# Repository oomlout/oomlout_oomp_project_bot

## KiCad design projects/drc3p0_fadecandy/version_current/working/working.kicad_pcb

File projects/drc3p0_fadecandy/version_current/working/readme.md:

# fadecandy by Drc3p0  
This is a harvested standardized copy of a project from github.  
The original project can be found at:  
https://github.com/Drc3p0/fadecandy  
Please consult that link for additional, details, files, and license information.  
Note: It was auto harvested and if the original repo had more than one board file or anything out of the ordinary the files here are likely not representative.

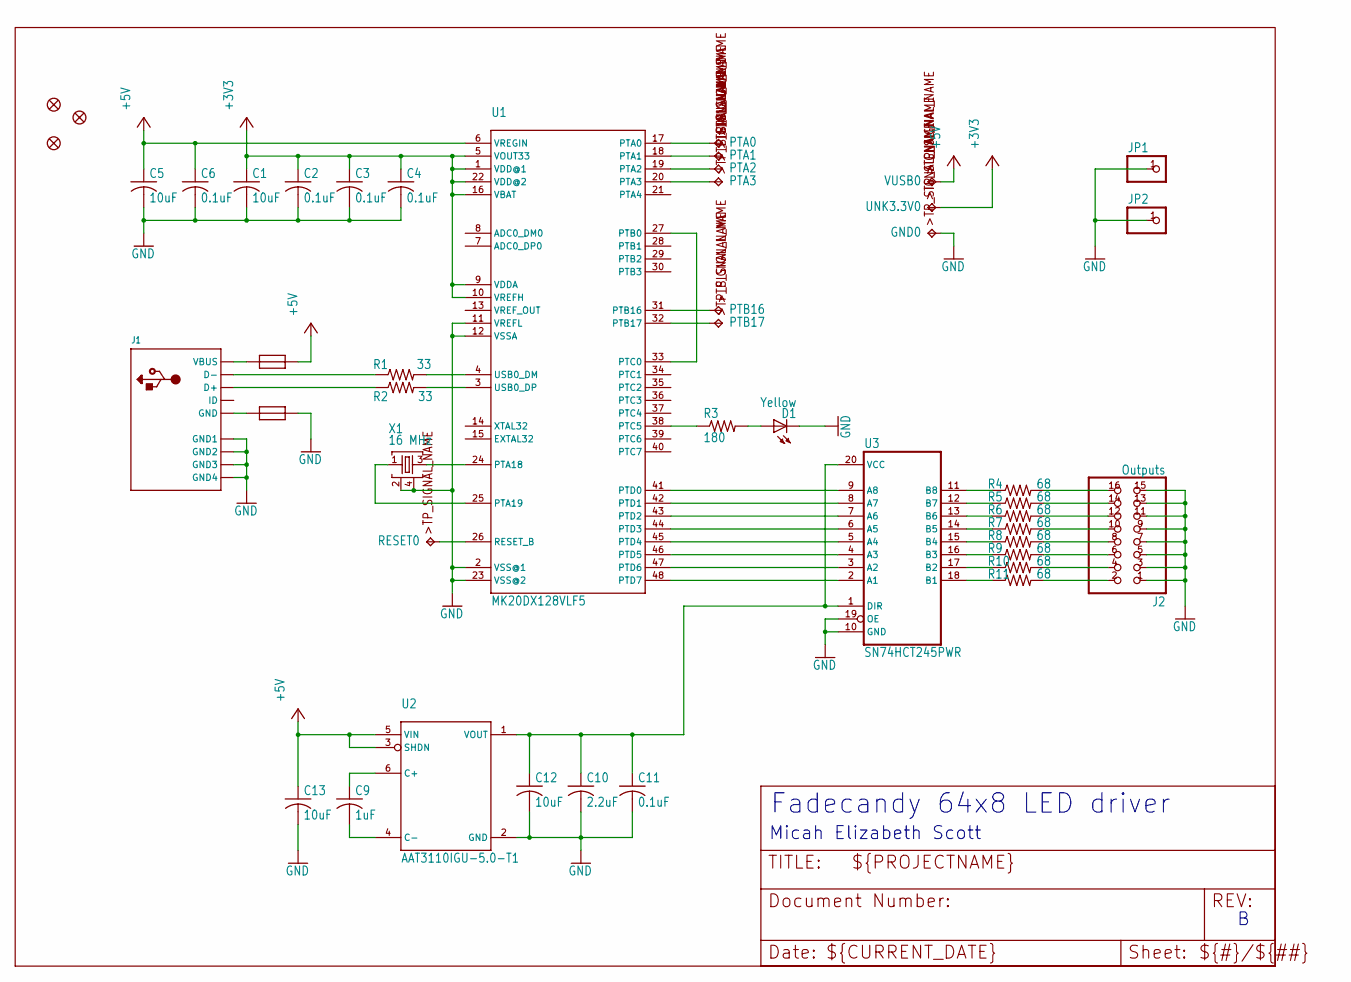
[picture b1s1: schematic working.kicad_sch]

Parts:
C1, C5, C12, C13: 10uF; 0805
C2, C3, C4, C6, C11: 0.1uF; 0805
C9: 1uF; 0805
C10: 2.2uF; 0805
D1: Yellow; CHIP-LED0805
FB1, FB2: FB0805/NO-OUTLINE; 0805
FID1, FID2, FID3: FIDUCIAL""; FIDUCIAL_1MM
GND0: TPTP18SQ; TP18SQ
J1: USBMINIB; USB-MINIB
J2: Outputs; 2X08
JP1, JP2: PINHD-1X1; 1X01
PTA0, PTA1, PTA2, PTA3: TPTP18SQ; TP18SQ
PTB16, PTB17: TPTP18SQ; TP18SQ
R1, R2: 33; 0805
R3: 180; 0805
R4, R5, R6, R7, R8, R9, R10, R11: 68; 0805
RESET0: TPTP18SQ; TP18SQ
U1: MK20DX128VLF5; LQFP48
U2: AAT3110IGU-5.0-T1; SOT23-6L
U3: SN74HCT245PWR; TSSOP20
UNK3.3V0: TPTP18SQ; TP18SQ
VUSB0: TPTP18SQ; TP18SQ
X1: 16 MHz; TSX-3225

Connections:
+3V3: C1.1, C2.1, C3.1, C4.1, U1.1 (VDD@1), U1.5 (VOUT33), U1.9 (VDDA), U1.10 (VREFH), U1.16 (VBAT), U1.22 (VDD@2), UNK3.3V0.TP
+5V: C5.1, C6.1, C13.1, FB1.2, U1.6 (VREGIN), U2.3 (SHDN), U2.5 (VIN), VUSB0.TP
GND: C1.2, C2.2, C3.2, C4.2, C5.2, C6.2, C10.2, C11.2, C12.2, C13.2, D1.C, FB2.2, GND0.TP, J1.GND1, J1.GND2, J1.GND3, J1.GND4, J2.1, J2.3, J2.5, J2.7, J2.9, J2.11, J2.13, J2.15, JP1.1, JP2.1, U1.2 (VSS@1), U1.11 (VREFL), U1.12 (VSSA), U1.23 (VSS@2), U2.2 (GND), U3.10 (GND), U3.19 (OE), X1.2, X1.4
unnamed: R3.1, U1.38 (PTC5)
unnamed: U1.24 (PTA18), X1.3
unnamed: D1.A, R3.2
unnamed: U1.25 (PTA19), X1.1
unnamed: FB1.1, J1.VBUS
unnamed: U1.27 (PTB0), U1.33 (PTC0)
unnamed: FB2.1, J1.GND
unnamed: U1.41 (PTD0), U3.9 (A8)
unnamed: J1.D-, R1.1
unnamed: J1.D+, R2.1
unnamed: R1.2, U1.4 (USB0_DM)
unnamed: R2.2, U1.3 (USB0_DP)
unnamed: U1.42 (PTD1), U3.8 (A7)
unnamed: U1.43 (PTD2), U3.7 (A6)
unnamed: U1.44 (PTD3), U3.6 (A5)
unnamed: U1.45 (PTD4), U3.5 (A4)
unnamed: U1.46 (PTD5), U3.4 (A3)
unnamed: U1.47 (PTD6), U3.3 (A2)
unnamed: U1.48 (PTD7), U3.2 (A1)
unnamed: R4.1, U3.11 (B8)
unnamed: C9.1, U2.6 (C+)
unnamed: C9.2, U2.4 (C-)
unnamed: R5.1, U3.12 (B7)
unnamed: R6.1, U3.13 (B6)
unnamed: R7.1, U3.14 (B5)
unnamed: R8.1, U3.15 (B4)
unnamed: C10.1, C11.1, C12.1, U2.1 (VOUT), U3.1 (DIR), U3.20 (VCC)
unnamed: R9.1, U3.16 (B3)
unnamed: R10.1, U3.17 (B2)
unnamed: R11.1, U3.18 (B1)
unnamed: J2.16, R4.2
unnamed: J2.14, R5.2
unnamed: J2.12, R6.2
unnamed: J2.10, R7.2
unnamed: J2.8, R8.2
unnamed: J2.6, R9.2
unnamed: J2.4, R10.2
unnamed: J2.2, R11.2
unnamed: RESET0.TP, U1.26 (RESET_B)
unnamed: PTA0.TP, U1.17 (PTA0)
unnamed: PTA1.TP, U1.18 (PTA1)
unnamed: PTA2.TP, U1.19 (PTA2)
unnamed: PTA3.TP, U1.20 (PTA3)
unnamed: PTB16.TP, U1.31 (PTB16)
unnamed: PTB17.TP, U1.32 (PTB17)

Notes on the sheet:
Micah Elizabeth Scott
Fadecandy 64x8 LED driver

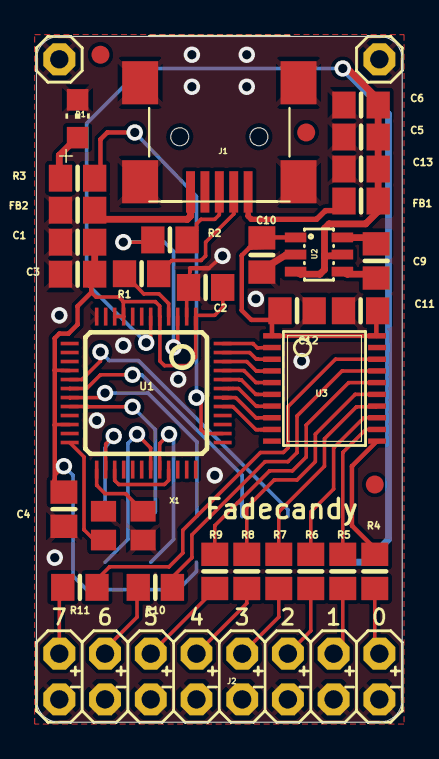
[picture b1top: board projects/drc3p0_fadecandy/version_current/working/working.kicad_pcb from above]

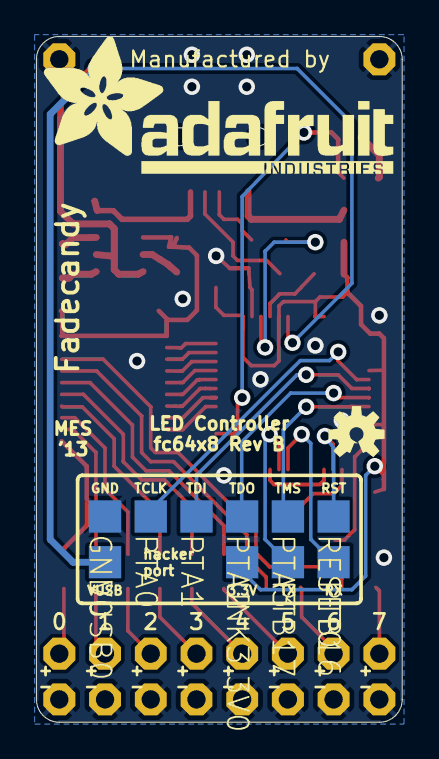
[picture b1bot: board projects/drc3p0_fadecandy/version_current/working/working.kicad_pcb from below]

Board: 16 copper layers, 20.3 x 38.1 mm, 48 parts (12 on the bottom side), 48 nets.

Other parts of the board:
U$1: OSHW-LOGO-S
U$2: ADAFRUIT_TEXT_20MM

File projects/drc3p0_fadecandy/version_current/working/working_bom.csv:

"Id";"Designator";"Footprint";"Quantity";"Designation";"Supplier and ref";
1;"R2,R1";"0805";2;"33";;;
2;"C4,C3,C11,C6,C2";"0805";5;"0.1uF";;;
3;"U3";"TSSOP20";1;"SN74HCT245PWR";;;
4;"FID2,FID1,FID3";"FIDUCIAL_1MM";3;"FIDUCIAL""";;;
5;"JP1,JP2";"1X01";2;"";;;
6;"U1";"LQFP48";1;"MK20DX128VLF5";;;
7;"R10,R6,R5,R8,R7,R11,R9,R4";"0805";8;"68";;;
8;"J2";"2X08";1;"Outputs";;;
9;"C13,C1,C5,C12";"0805";4;"10uF";;;
10;"J1";"USB-MINIB";1;"";;;
11;"R3";"0805";1;"180";;;
12;"X1";"TSX-3225";1;"16 MHz";;;
13;"FB2,FB1";"0805";2;"FB0805/NO-OUTLINE";;;
14;"D1";"CHIP-LED0805";1;"Yellow";;;
15;"C9";"0805";1;"1uF";;;
16;"C10";"0805";1;"2.2uF";;;
17;"U2";"SOT23-6L";1;"AAT3110IGU-5.0-T1";;;
18;"PTB17,VUSB0,RESET0,UNK3.3V0,PTA2,PTA1,PTB16,PTA0,GND0,PTA3";"TP18SQ";10;"TPTP18SQ";;;
19;"U$1";"OSHW-LOGO-S";1;"";;;
20;"U$2";"ADAFRUIT_TEXT_20MM";1;"";;;

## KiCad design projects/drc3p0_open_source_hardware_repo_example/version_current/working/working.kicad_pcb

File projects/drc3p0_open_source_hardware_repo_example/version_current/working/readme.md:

# open-source-hardware-repo-example by Drc3p0  
This is a harvested standardized copy of a project from github.  
The original project can be found at:  
https://github.com/Drc3p0/open-source-hardware-repo-example  
Please consult that link for additional, details, files, and license information.  
Note: It was auto harvested and if the original repo had more than one board file or anything out of the ordinary the files here are likely not representative.

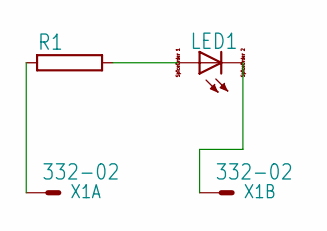
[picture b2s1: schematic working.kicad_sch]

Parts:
LED1: LED_ELD260; LED_LD260
R1: RAC01; AC01
X1: 332-02

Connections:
unnamed: LED1.A, R1.2
unnamed: R1.1, X1.1
unnamed: LED1.K (C), X1.2

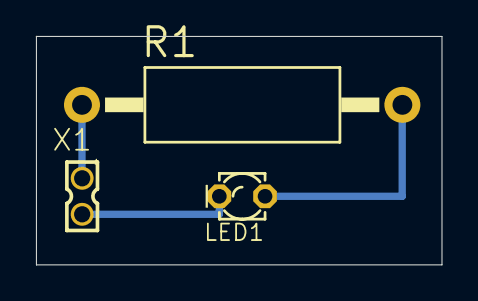
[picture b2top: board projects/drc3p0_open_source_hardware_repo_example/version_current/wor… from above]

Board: 2 copper layers, 22.5 x 12.7 mm, 3 parts (0 on the bottom side), 3 nets.

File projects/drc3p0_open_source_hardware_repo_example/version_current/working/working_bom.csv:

"Id";"Designator";"Footprint";"Quantity";"Designation";"Supplier and ref";
1;"X1";"332-02";1;"332-02";;;
2;"R1";"AC01";1;"";;;
3;"LED1";"LED_LD260";1;"";;;

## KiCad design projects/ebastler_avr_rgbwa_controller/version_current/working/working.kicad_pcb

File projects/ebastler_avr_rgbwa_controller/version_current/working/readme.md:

# AVR-RGBWA-Controller by ebastler  
This is a harvested standardized copy of a project from github.  
The original project can be found at:  
https://github.com/ebastler/AVR-RGBWA-Controller  
Please consult that link for additional, details, files, and license information.  
Note: It was auto harvested and if the original repo had more than one board file or anything out of the ordinary the files here are likely not representative.

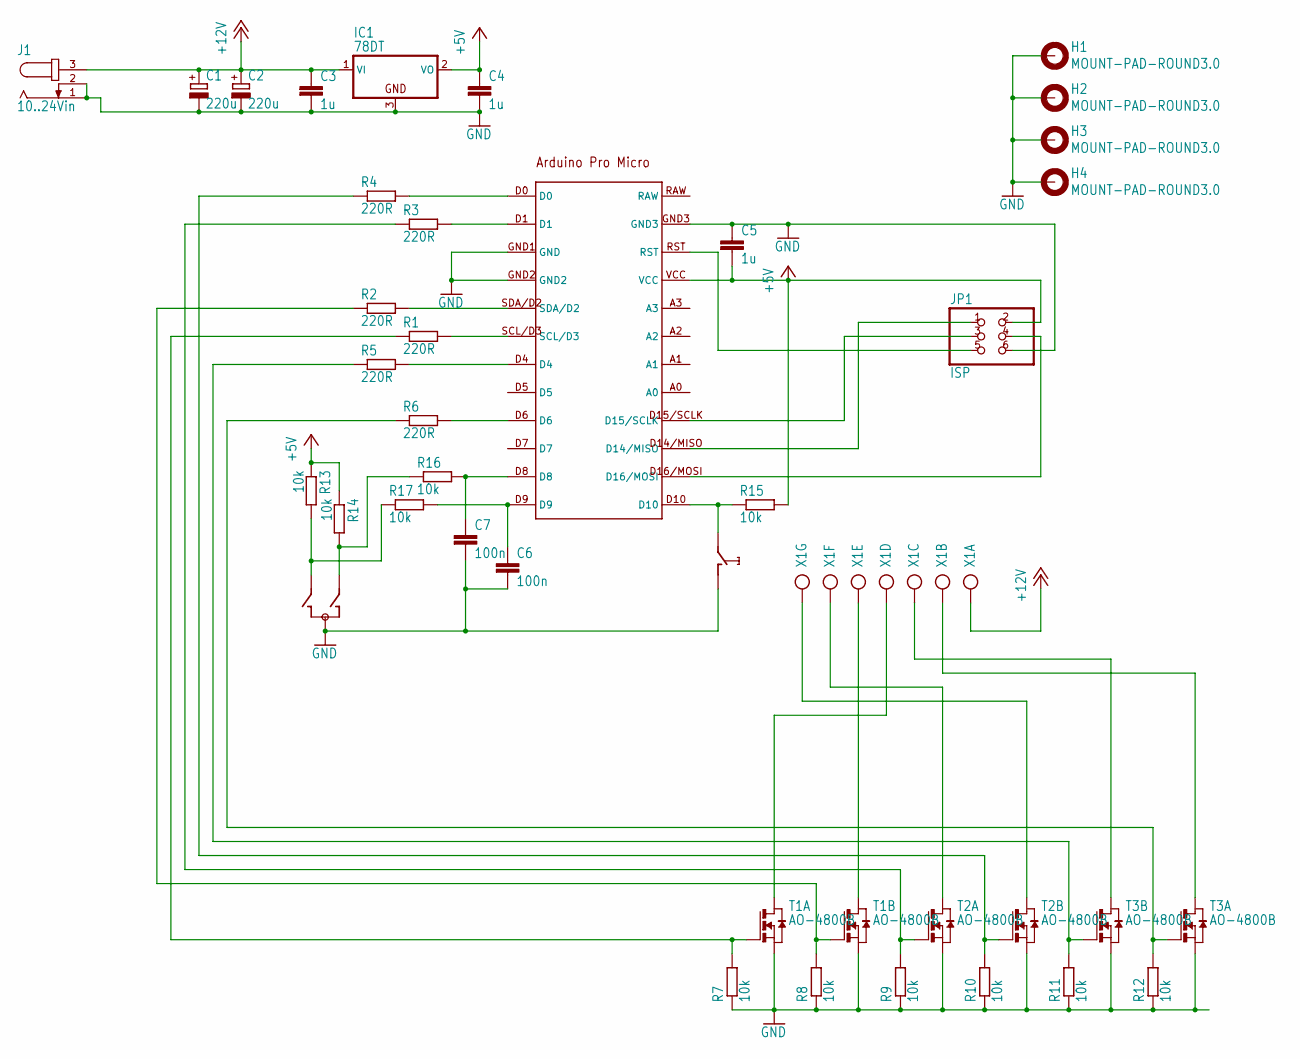
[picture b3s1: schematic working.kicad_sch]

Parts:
C1, C2: 220u; 150CLZ-1010
C3, C4, C5: 1u; C1206
C6, C7: 100n; C0805
H1, H2, H3, H4: MOUNT-PAD-ROUND3.0; 3,0-PAD
IC1: 78DT; TO252
J1: 10..24Vin; SPC4078
JP1: ISP; 2X03
R1, R2, R3, R4, R5, R6: 220R; M0805
R7, R8, R9, R10, R11, R12, R13, R14, R15, R16, R17: 10k; M0805
SW1: EC12E_SW; ALPS_EC12E_SW
T1, T2, T3: AO-4800B; SM8
U$1: PROMICRO
X1: AK300/7; AK300_7

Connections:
+5V: C4.1, C5.2, IC1.2 (VO), JP1.2, R13.1, R14.1, R15.2, U$1.VCC
+12V: C1.+, C2.+, C3.1, IC1.1 (VI), J1.3, X1.1
GND: C1.-, C2.-, C3.2, C4.2, C5.1, C6.2, C7.2, H1.B3,0, H2.B3,0, H3.B3,0, H4.B3,0, IC1.3 (GND), J1.1, J1.2, JP1.6, R7.1, R8.1, R9.1, R10.1, R11.1, R12.1, SW1.C, SW1.D (1), T1.1 (S), T1.3 (S), T2.1 (S), T2.3 (S), T3.1 (S), T3.3 (S), U$1.GND1 (GND), U$1.GND2, U$1.GND3
unnamed: R4.2, U$1.D0
unnamed: R3.2, U$1.D1
unnamed: R2.2, U$1.SDA/D2
unnamed: R1.2, U$1.SCL/D3
unnamed: R5.2, U$1.D4
unnamed: R6.2, U$1.D6
unnamed: R1.1, R7.2, T1.2 (G)
unnamed: R2.1, R8.2, T1.4 (G)
unnamed: R3.1, R9.2, T2.2 (G)
unnamed: R4.1, R10.2, T2.4 (G)
unnamed: R5.1, R11.2, T3.4 (G)
unnamed: R6.1, R12.2, T3.2 (G)
unnamed: R13.2, R17.1, SW1.B
unnamed: JP1.1, U$1.D14/MISO
unnamed: T3.7 (D), T3.8 (D), X1.2
unnamed: T1.5 (D), T1.6 (D), X1.5
unnamed: T1.7 (D), T1.8 (D), X1.4
unnamed: R14.2, R16.1, SW1.A
unnamed: JP1.3, U$1.D15/SCLK
unnamed: C6.1, R17.2, U$1.D9
unnamed: R15.1, SW1.E (2), U$1.D10
unnamed: C7.1, R16.2, U$1.D8
unnamed: JP1.5, U$1.RST
unnamed: T3.5 (D), T3.6 (D), X1.3
unnamed: T2.5 (D), T2.6 (D), X1.7
unnamed: T2.7 (D), T2.8 (D), X1.6
unnamed: JP1.4, U$1.D16/MOSI

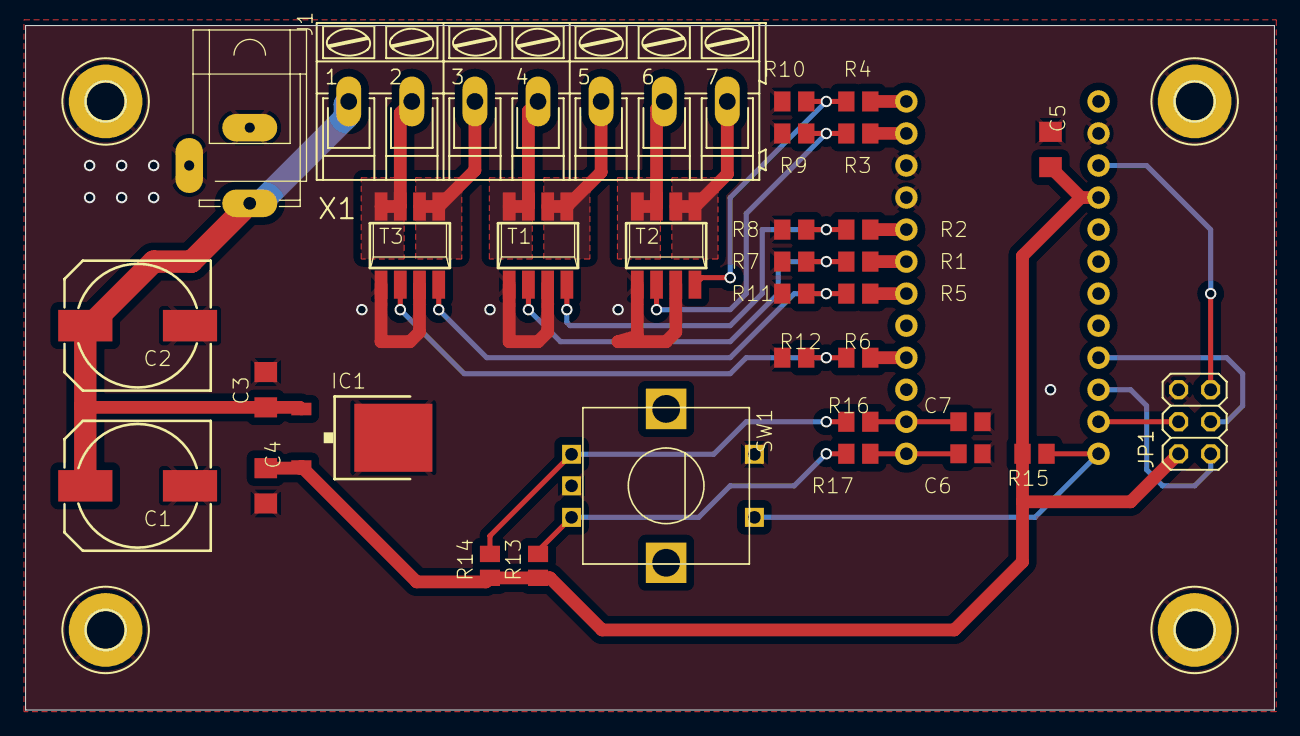
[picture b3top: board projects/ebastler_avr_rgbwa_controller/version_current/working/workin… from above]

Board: 2 copper layers, 99.0 x 54.3 mm, 37 parts (0 on the bottom side), 30 nets.

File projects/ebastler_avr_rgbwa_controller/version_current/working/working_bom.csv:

"Id";"Designator";"Footprint";"Quantity";"Designation";"Supplier and ref";
1;"T1,T2,T3";"SM8";3;"AO-4800B";;;
2;"R16,R15,R10,R7,R9,R8,R11,R17,R13,R12,R14";"M0805";11;"10k";;;
3;"R5,R3,R6,R1,R4,R2";"M0805";6;"220R";;;
4;"C1,C2";"150CLZ-1010";2;"220u";;;
5;"C5,C3,C4";"C1206";3;"1u";;;
6;"C6,C7";"C0805";2;"100n";;;
7;"H2,H4,H1,H3";"3,0-PAD";4;"MOUNT-PAD-ROUND3.0";;;
8;"X1";"AK300_7";1;"";;;
9;"JP1";"2X03";1;"ISP";;;
10;"J1";"SPC4078";1;"10..24Vin";;;
11;"SW1";"ALPS_EC12E_SW";1;"EC12E_SW";;;
12;"U$1";"PROMICRO";1;"PROMICRO";;;
13;"IC1";"TO252";1;"7805DT";;;

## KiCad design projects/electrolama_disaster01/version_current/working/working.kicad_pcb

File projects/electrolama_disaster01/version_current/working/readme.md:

# OOMP Project  
## disaster01  by electrolama  
  
oomp key: oomp_projects_flat_electrolama_disaster01  
(snippet of original readme)  
  
- disaster01  
overly blinky thing debuted at Hackaday Supercon 2019  
  
Details at [electrolama.com/p/disaster01](https://electrolama.com/p/disaster01/).  
  
  full source readme at [readme_src.md](readme_src.md)  
  
source repo at: [https://github.com/electrolama/disaster01](https://github.com/electrolama/disaster01)  
## Board  

## Schematic  

[schematic pdf](working_schematic.pdf)  
## Images

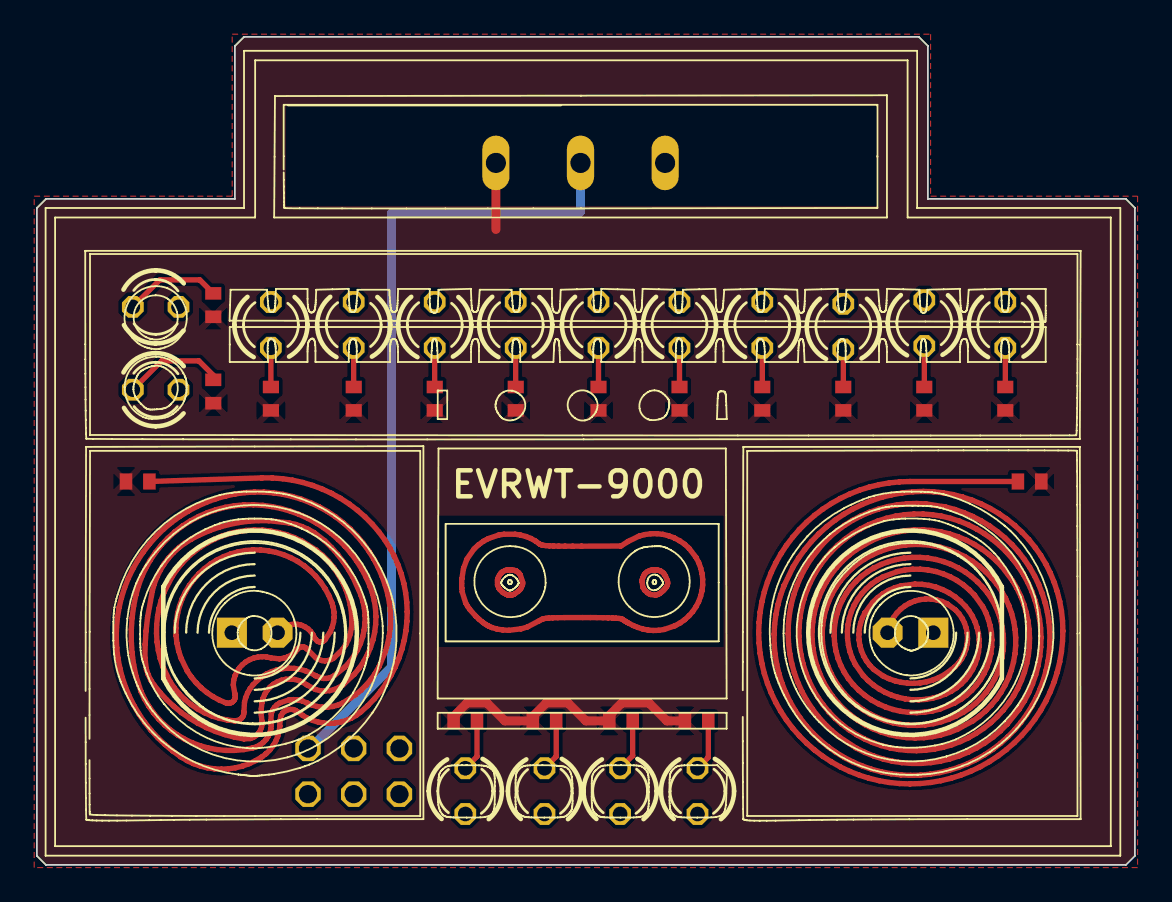
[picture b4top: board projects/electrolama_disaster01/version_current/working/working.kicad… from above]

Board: 2 copper layers, 61.0 x 46.0 mm, 38 parts (0 on the bottom side), 21 nets.

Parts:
JP1: 2X03
LED1, LED3, LED4, LED5, LED6, LED7, LED8, LED9, LED10, LED11, LED12, LED13, LED14, LED15, LED16, LED17: LED3MM
LED2, LED18: LED10MM
R1, R2, R3, R4, R5, R6, R7, R8, R9, R10, R11, R12, R13, R14, R15, R16, R17, R18: R0402
S1: 255SB

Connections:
3.3V: R1.1, R2.1, R3.1, R4.1, R5.1, R6.1, R7.1, R8.1, R9.1, R10.1, R11.1, R12.1, R13.1, R14.1, R15.1, R16.1, R17.1, R18.1, S1.1
GND: JP1.1, LED1.K, LED2.K, LED3.K, LED4.K, LED5.K, LED6.K, LED7.K, LED8.K, LED9.K, LED10.K, LED11.K, LED12.K, LED13.K, LED14.K, LED15.K, LED16.K, LED17.K, LED18.K
unnamed: LED1.A, R1.2
unnamed: LED2.A, R2.2
unnamed: LED3.A, R3.2
unnamed: LED4.A, R4.2
unnamed: LED5.A, R5.2
unnamed: LED6.A, R6.2
unnamed: LED7.A, R7.2
unnamed: LED8.A, R8.2
unnamed: LED9.A, R9.2
unnamed: LED10.A, R10.2
unnamed: LED11.A, R11.2
unnamed: LED12.A, R12.2
unnamed: LED13.A, R13.2
unnamed: LED14.A, R14.2
unnamed: LED15.A, R15.2
unnamed: LED16.A, R16.2
unnamed: LED17.A, R17.2
unnamed: LED18.A, R18.2
unnamed: JP1.2, S1.2

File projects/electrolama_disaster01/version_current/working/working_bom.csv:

"Id";"Designator";"Footprint";"Quantity";"Designation";"Supplier and ref";
1;"S1";"255SB";1;"";;;
2;"LED17,LED10,LED3,LED9,LED8,LED12,LED14,LED6,LED15,LED5,LED1,LED7,LED4,LED11,LED13,LED16";"LED3MM";16;"";;;
3;"R13,R10,R12,R9,R18,R3,R16,R4,R17,R5,R11,R1,R15,R7,R14,R8,R2,R6";"R0402";18;"";;;
4;"JP1";"2X03";1;"";;;
5;"LED2,LED18";"LED10MM";2;"";;;

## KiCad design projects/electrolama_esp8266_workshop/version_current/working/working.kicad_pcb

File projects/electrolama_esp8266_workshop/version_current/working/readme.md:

# OOMP Project  
## esp8266-workshop  by electrolama  
  
oomp key: oomp_projects_flat_electrolama_esp8266_workshop  
(snippet of original readme)  
  
- esp8266-workshop  
  
  full source readme at [readme_src.md](readme_src.md)  
  
source repo at: [https://github.com/electrolama/esp8266-workshop](https://github.com/electrolama/esp8266-workshop)  
## Board  

## Schematic  

[schematic pdf](working_schematic.pdf)  
## Images

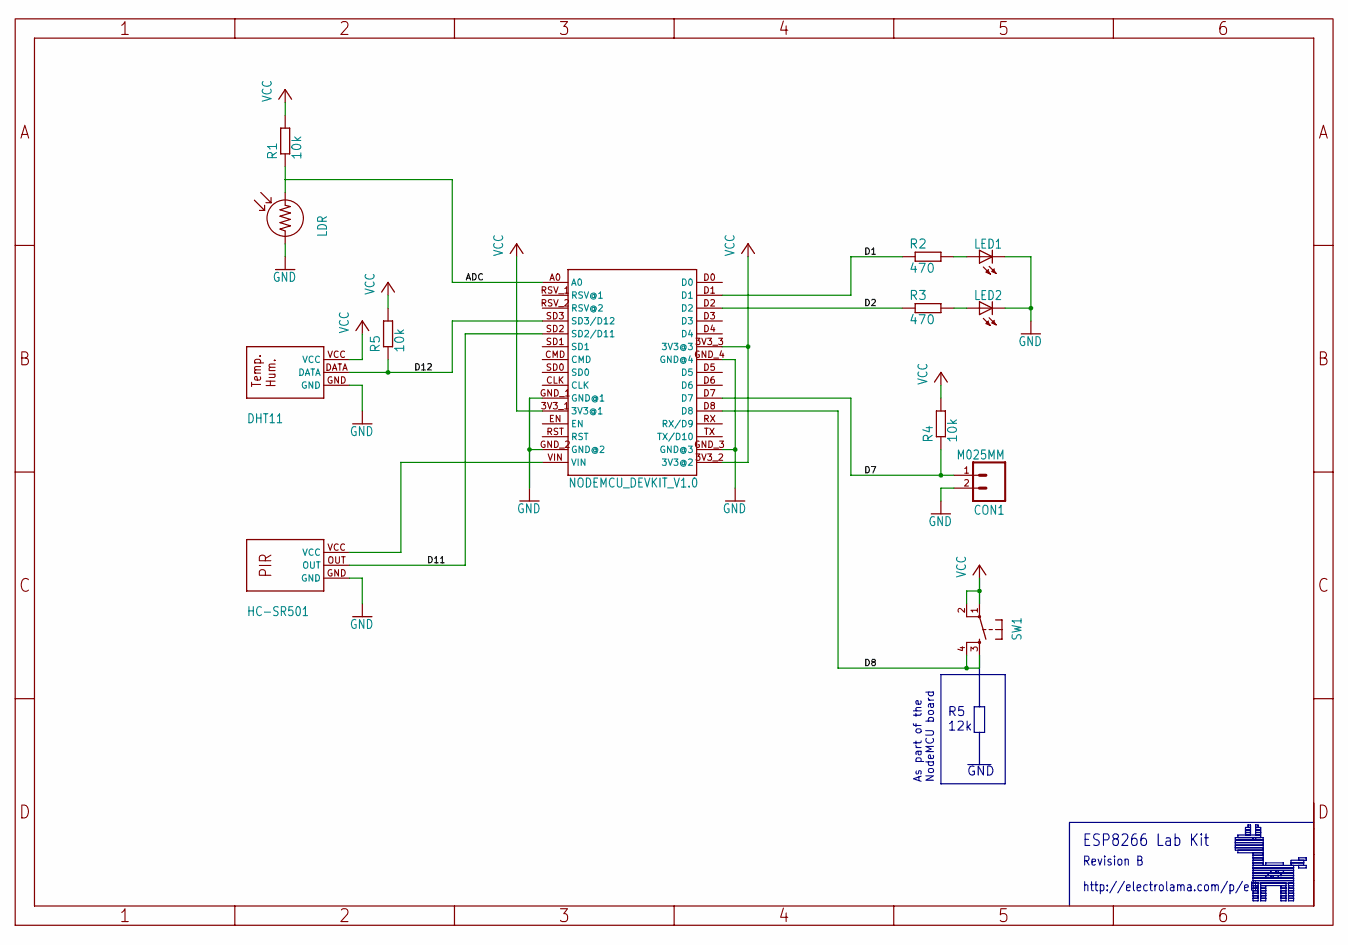
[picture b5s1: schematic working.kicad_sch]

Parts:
CON1: M025MM; SCREWTERMINAL-5MM-2
LED1, LED2: LED5MM
R1, R4, R5: 10k; RTH025W
R2, R3: 470; RTH025W
SW1: TAC_SWITCHPTH; TACTILE-PTH
U1: NODEMCU_DEVKIT_V1.0
U2: DHT11
U3: HC-SR501
VR1: LDR

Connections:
ADC: R1.1, U1.A0, VR1.2
D1: R2.1, U1.D1
D2: R3.1, U1.D2
D7: CON1.1, R4.1, U1.D7
D8: SW1.3, SW1.4, U1.D8
D11: U1.SD2 (SD2/D11), U3.OUT
D12: R5.1, U1.SD3 (SD3/D12), U2.DATA
GND: CON1.2, LED1.K (C), LED2.K (C), U1.GND_1 (GND@1), U1.GND_2 (GND@2), U1.GND_3 (GND@3), U1.GND_4 (GND@4), U2.GND, U3.GND, VR1.1
unnamed: LED1.A, R2.2
unnamed: LED2.A, R3.2
unnamed: U1.VIN, U3.VCC
VCC: R1.2, R4.2, R5.2, SW1.1, SW1.2, U1.3V3_1 (3V3@1), U1.3V3_2 (3V3@2), U1.3V3_3 (3V3@3), U2.VCC

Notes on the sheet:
Revision B
http://electrolama.com/p/elk
GND
As part of the NodeMCU board
R5 12k
ESP8266 Lab Kit

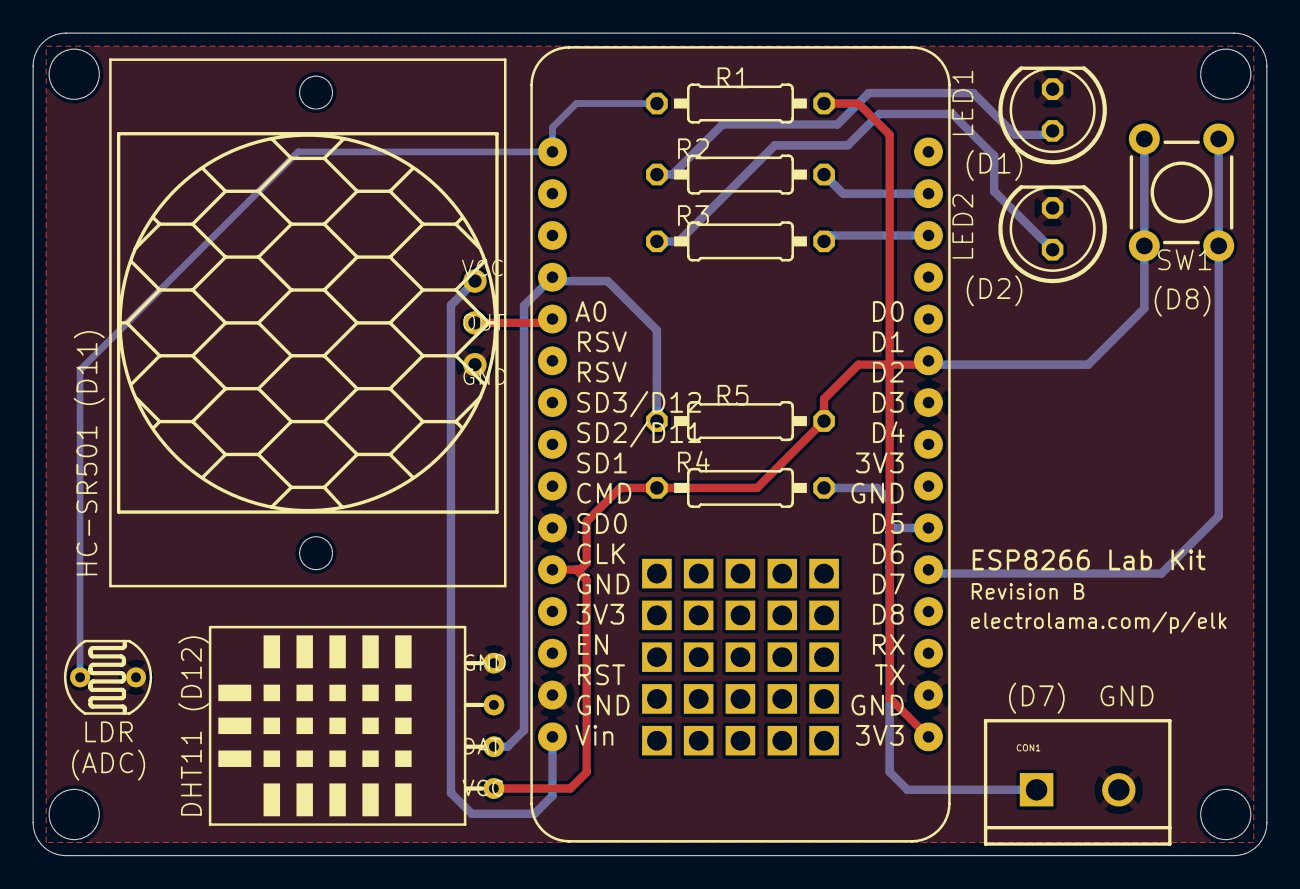
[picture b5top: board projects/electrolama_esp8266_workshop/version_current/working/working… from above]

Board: 2 copper layers, 75.0 x 50.0 mm, 18 parts (0 on the bottom side), 12 nets.

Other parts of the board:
@HOLE0, @HOLE1, @HOLE2, @HOLE3: (no value)
U$1: PROTO_VIAS_05X05-1.2; PROTO_VIAS_05X05_1.2

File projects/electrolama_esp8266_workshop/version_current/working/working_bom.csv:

Row,Description,Part,References,Value,Footprint,Quantity Per PCB,Status,Datasheet
1,,M025MM,CON1,M025MM,SCREWTERMINAL-5MM-2,1, ,
2,,LED5MM,LED1 LED2,LED5MM,LED5MM,2, ,
3,,RESISTOR-PTH-0.4,R2 R3,470,RTH025W,2, ,
4,,RESISTOR-PTH-0.4,R1 R4 R5,10k,RTH025W,3, ,
5,,TAC_SWITCHPTH,SW1,TAC_SWITCHPTH,TACTILE-PTH,1, ,
6,,DHT11,U2,DHT11,DHT11,1, ,
7,,HC-SR501,U3,HC-SR501,HC-SR501,1, ,
8,,NODEMCU_DEVKIT_V1.0,U1,NODEMCU_DEVKIT_V1.0,NODEMCU_DEVKIT_V1.0,1, ,
9,,LDR,VR1,LDR,LDR,1, ,





Project info:
Schematic:,working
Variant:,default
Revision:,
Date:,2023-08-03_17-21-23
KiCad Version:,7.0.6-7.0.6~ubuntu22.04.1
Statistics:
Component Groups:,9
Component Count:,13 (0 SMD/ 0 THT)
Fitted Components:,13 (0 SMD/ 0 THT)
Number of PCBs:,1
Total Components:,13

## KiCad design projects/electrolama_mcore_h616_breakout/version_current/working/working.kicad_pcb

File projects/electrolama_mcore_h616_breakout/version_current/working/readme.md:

# mcore-h616-breakout by electrolama  
This is a harvested standardized copy of a project from github.  
The original project can be found at:  
https://github.com/electrolama/mcore-h616-breakout  
Please consult that link for additional, details, files, and license information.  
Note: It was auto harvested and if the original repo had more than one board file or anything out of the ordinary the files here are likely not representative.

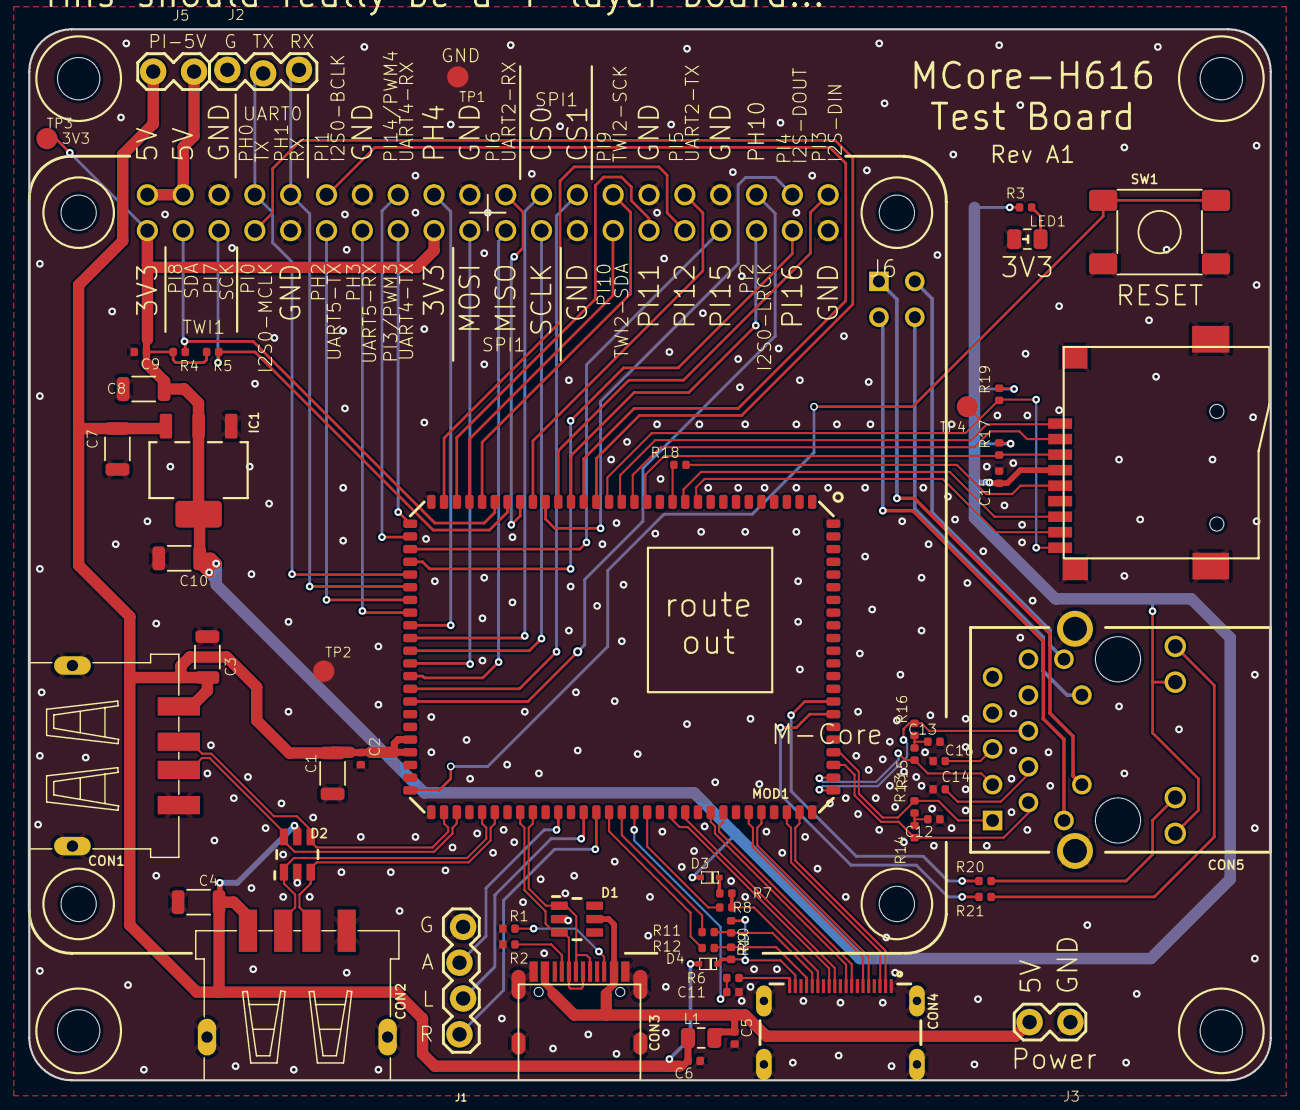
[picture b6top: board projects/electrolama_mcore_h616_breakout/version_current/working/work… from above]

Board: 2 copper layers, 88.0 x 74.5 mm, 70 parts (0 on the bottom side), 88 nets.

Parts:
@HOLE0, @HOLE1, @HOLE2, @HOLE3, @HOLE4, @HOLE5, @HOLE6, @HOLE7: (no value)
C1, C3, C4, C7, C8, C10: 47u; _PKG_C_1206
C2, C6, C9, C11, C12, C13, C14, C15, C16: 100n; _PKG_C_0402
C5: 10n; _PKG_C_0402
CON1, CON2: JING_912-121A2023S10100
CON3: USBC_C-31-M-12
CON4: C136421 - HDMI-519; 685119136923
CON5: LPJG0926HENL
CON6: C111196 - TF-15x15; TF_SHENZHEN-SPECIAL
D1, D2: SRV05-4-P-T7; SOT95P280X145-6N
D3, D4: RB520S30T1G; _PKG_SOD523
IC1: LD1117-3.3; _PKG_SOT223-4_TI-DCY4
J1: 1X04_LOCK
J2: 1X03_LOCK
J3, J5: 1X02_LOCK
J4: CON_2.54MM_TH_2X20
J6: CON_2.54MM_TH_2X2
L1: FB; _PKG_C_0805
LED1: _PKG_LED_0805
MOD1: MCORE-H616_V1
R1, R2: 5k1; _PKG_R_0402
R3, R8, R11, R12, R18, R20, R21: 100; _PKG_R_0402
R4, R5, R17, R19: 10k; _PKG_R_0402
R6: 1k; _PKG_R_0402
R7: 27k 1%; _PKG_R_0402
R9, R10: 1k8; _PKG_R_0402
R13, R14, R15, R16: 49.9Ω; _PKG_R_0402
SW1: SPNO; GENERIC_SPNO_4P_6X6MM
TP1, TP2, TP3, TP4: TP; TP_DOT_1.5X1.5MM

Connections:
5V: C1.2, C2.2, C3.2, C4.2, C6.2, C7.2, CON1.VBUS, CON2.VBUS, D2.5, D4.2, IC1.3, J5.2, L1.2, MOD1.49, MOD1.50
GND: C1.1, C2.1, C3.1, C4.1, C5.1, C6.1, C7.1, C8.1, C9.1, C10.1, C11.1, C12.1, C13.1, C14.1, C15.1, C16.1, CON1.GND, CON1.P$5, CON1.P$6, CON2.GND, CON2.P$5, CON2.P$6, CON3.GND@1, CON3.GND@2, CON3.P$1, CON3.P$2, CON3.P$3, CON3.P$4, CON3.P$5, CON3.P$6, CON3.P$7, CON3.P$8, CON4.1, CON4.4, CON4.7, CON4.10, CON4.13, CON4.SHELL, CON4.SHELL1, CON4.SHELL2, CON4.SHELL3, CON5.MH3, CON5.MH4, CON6.6, CON6.S1, CON6.S2, CON6.S3, CON6.S4, D1.2, D2.2, IC1.1, J1.1, J2.1, J3.1, J4.P$6, J4.P$9, J4.P$14, J4.P$20, J4.P$25, J4.P$30, J4.P$34, J4.P$39, LED1.C, MOD1.13, MOD1.31, MOD1.51, MOD1.52, MOD1.54, MOD1.57, MOD1.60, MOD1.63, MOD1.72, MOD1.75, MOD1.78, MOD1.81, MOD1.84, MOD1.89, MOD1.106, R1.1, R2.1, SW1.P$3, SW1.P$4, TP1.TP, TP2.TP
H5V: CON4.18, D4.1, R9.1, R10.1
HCEC: MOD1.71, R8.2
HDCEC: CON4.14, R7.1, R8.1
HDHPD: CON4.19, R6.1
HDSCL: CON4.15, R9.2, R11.1
HDSDA: CON4.16, R10.2, R12.1
HHPD: C11.2, MOD1.70, R6.2
HSCL: MOD1.69, R11.2
HSDA: MOD1.68, R12.2
HTX0_N: CON4.9, MOD1.76
HTX0_P: CON4.8, MOD1.77
HTX1_N: CON4.6, MOD1.79
HTX1_P: CON4.5, MOD1.80
HTX2_N: CON4.3, MOD1.82
HTX2_P: CON4.2, MOD1.83
HTXC_N: CON4.12, MOD1.73
HTXC_P: CON4.11, MOD1.74
LAN_LED_G: MOD1.92, R20.2
LAN_LED_Y: MOD1.91, R21.2
LINEOUT_L: J1.3, MOD1.66
LINEOUT_R: J1.4, MOD1.67
LRADC: J1.2, MOD1.64
unnamed: LED1.A, R3.1
unnamed: CON5.16, R20.1
unnamed: C14.2, CON5.4
unnamed: C16.2, CON5.5
unnamed: J4.P$2, J4.P$4, J5.1
unnamed: CON5.18, R21.1
unnamed: D3.1, R7.2
unnamed: CON3.CC1, R2.2
unnamed: CON3.CC2, R1.2
unnamed: C12.2, R13.1, R14.1
unnamed: C13.2, R15.1, R16.1
PH0/UART0-TX: J2.2, J4.P$8, MOD1.36
PH1/UART0-RX: J2.3, J4.P$10, MOD1.37
PH2/UART5-TX: J4.P$11, MOD1.38
PH3/UART5-RX: J4.P$13, MOD1.39
PH4: J4.P$18, MOD1.40
PH10: J4.P$36, MOD1.46
PI0/I2S0-MCLK: J4.P$7, MOD1.18
PI1/I2S0-BCLK: J4.P$12, MOD1.19
PI2/I2S0-LRCK: J4.P$35, MOD1.20
PI3/I2S0-DIN: J4.P$40, MOD1.21
PI4/I2S0-DOUT: J4.P$38, MOD1.22
PI5/UART2-TX: J4.P$32, MOD1.23
PI6/UART2-RX: J4.P$22, MOD1.24
PI7/TWI1-SCK: J4.P$5, MOD1.25, R5.2
PI8/TWI1-SDA: J4.P$3, MOD1.26, R4.2
PI9/TWI2-SCK: J4.P$28, MOD1.27
PI10/TWI2-SDA: J4.P$27, MOD1.28
PI11: J4.P$29, MOD1.29
PI12: J4.P$31, MOD1.30
PI13/UART4-TX/PWM3: J4.P$15, MOD1.32
PI14/UART4-RX/PWM4: J4.P$16, MOD1.33
PI15: J4.P$33, MOD1.34
PI16: J4.P$37, MOD1.35
RESET: MOD1.53, SW1.P$1, SW1.P$2
RXI_N: CON5.6, MOD1.85, R16.2
RXI_P: CON5.3, MOD1.86, R15.2
SCD0-CLK: MOD1.12, R18.2
SCD0-CLK': CON6.5, R18.1
SCD0-CMD: CON6.3, MOD1.14, R17.1
SCD0-D0: CON6.7, MOD1.11
SCD0-D1: CON6.8, MOD1.10
SCD0-D2: CON6.1, MOD1.16
SCD0-D3: CON6.2, MOD1.15
SCD0-DET: CON6.9, MOD1.17, R19.1, TP4.TP
SPI1-CLK: J4.P$23, MOD1.42
SPI1-CS0: J4.P$24, MOD1.41
SPI1-CS1: J4.P$26, MOD1.45
SPI1-MISO: J4.P$21, MOD1.44
SPI1-MOSI: J4.P$19, MOD1.43
TR0_TAP: CON5.11, J6.2
TR1_TAP: CON5.12, J6.1
TR2_TAP: CON5.13, J6.4
TR3_TAP: CON5.14, J6.3
TXO_N: CON5.2, MOD1.87, R14.2
TXO_P: CON5.1, MOD1.88, R13.2
USB0_N: CON3.DN1, CON3.DN2, D1.3, MOD1.61
USB0_P: CON3.DP1, CON3.DP2, D1.1, MOD1.62
USB1_N: CON1.DM, D2.4, MOD1.55
USB1_P: CON1.DP, D2.6, MOD1.56
USB2_N: CON2.DM, D2.1, MOD1.58
USB2_P: CON2.DP, D2.3, MOD1.59
VCC: C8.2, C9.2, C10.2, C15.2, CON5.15, CON5.17, CON6.4, D3.2, IC1.2, IC1.4, J4.P$1, J4.P$17, R3.2, R4.1, R5.1, R17.2, R19.2, TP3.TP
VUSB_IN: C5.2, CON3.VBUS@1, CON3.VBUS@2, D1.5, J3.2, L1.1

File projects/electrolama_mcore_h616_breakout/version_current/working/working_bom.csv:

"Id";"Designator";"Footprint";"Quantity";"Designation";"Supplier and ref";
1;"C8,C7,C1,C3,C10,C4";"_PKG_C_1206";6;"47u";;;
2;"R4,R5,R17,R19";"_PKG_R_0402";4;"10k";;;
3;"@HOLE7,@HOLE6,@HOLE1,@HOLE5,@HOLE2,@HOLE4,@HOLE3,@HOLE0";"";8;"";;;
4;"R18,R21,R12,R8,R20,R3,R11";"_PKG_R_0402";7;"100";;;
5;"C15,C14,C16,C11,C9,C2,C13,C12,C6";"_PKG_C_0402";9;"100n";;;
6;"SW1";"GENERIC_SPNO_4P_6X6MM";1;"SPNO";;;
7;"CON1,CON2";"JING_912-121A2023S10100";2;"";;;
8;"IC1";"_PKG_SOT223-4_TI-DCY4";1;"LD1117-3.3";;;
9;"R16,R15,R13,R14";"_PKG_R_0402";4;"49.9Ω";;;
10;"CON3";"USBC_C-31-M-12";1;"";;;
11;"J4";"CON_2.54MM_TH_2X20";1;"";;;
12;"R1,R2";"_PKG_R_0402";2;"5k1";;;
13;"CON6";"TF_SHENZHEN-SPECIAL";1;"C111196 - TF-15x15";;;
14;"D3,D4";"_PKG_SOD523";2;"RB520S30T1G";;;
15;"J3,J5";"1X02_LOCK";2;"";;;
16;"TP3,TP4,TP2,TP1";"TP_DOT_1.5X1.5MM";4;"TP";;;
17;"R6";"_PKG_R_0402";1;"1k";;;
18;"L1";"_PKG_C_0805";1;"FB";;;
19;"R10,R9";"_PKG_R_0402";2;"1k8";;;
20;"MOD1";"MCORE-H616_V1";1;"";;;
21;"J2";"1X03_LOCK";1;"";;;
22;"D2,D1";"SOT95P280X145-6N";2;"SRV05-4-P-T7";;;
23;"J6";"CON_2.54MM_TH_2X2";1;"";;;
24;"LED1";"_PKG_LED_0805";1;"";;;
25;"C5";"_PKG_C_0402";1;"10n";;;
26;"CON4";"685119136923";1;"C136421 - HDMI-519";;;
27;"CON5";"LPJG0926HENL";1;"LPJG0926HENL";;;
28;"R7";"_PKG_R_0402";1;"27k 1%";;;
29;"J1";"1X04_LOCK";1;"";;;
